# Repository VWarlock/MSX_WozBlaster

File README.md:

# MSX WozBlaster
MSX OPL4 FM &amp; Wavetable Sound Synthesizer

# WozBlaster version 1 Revision 2

All thruhole components was changed to SMT

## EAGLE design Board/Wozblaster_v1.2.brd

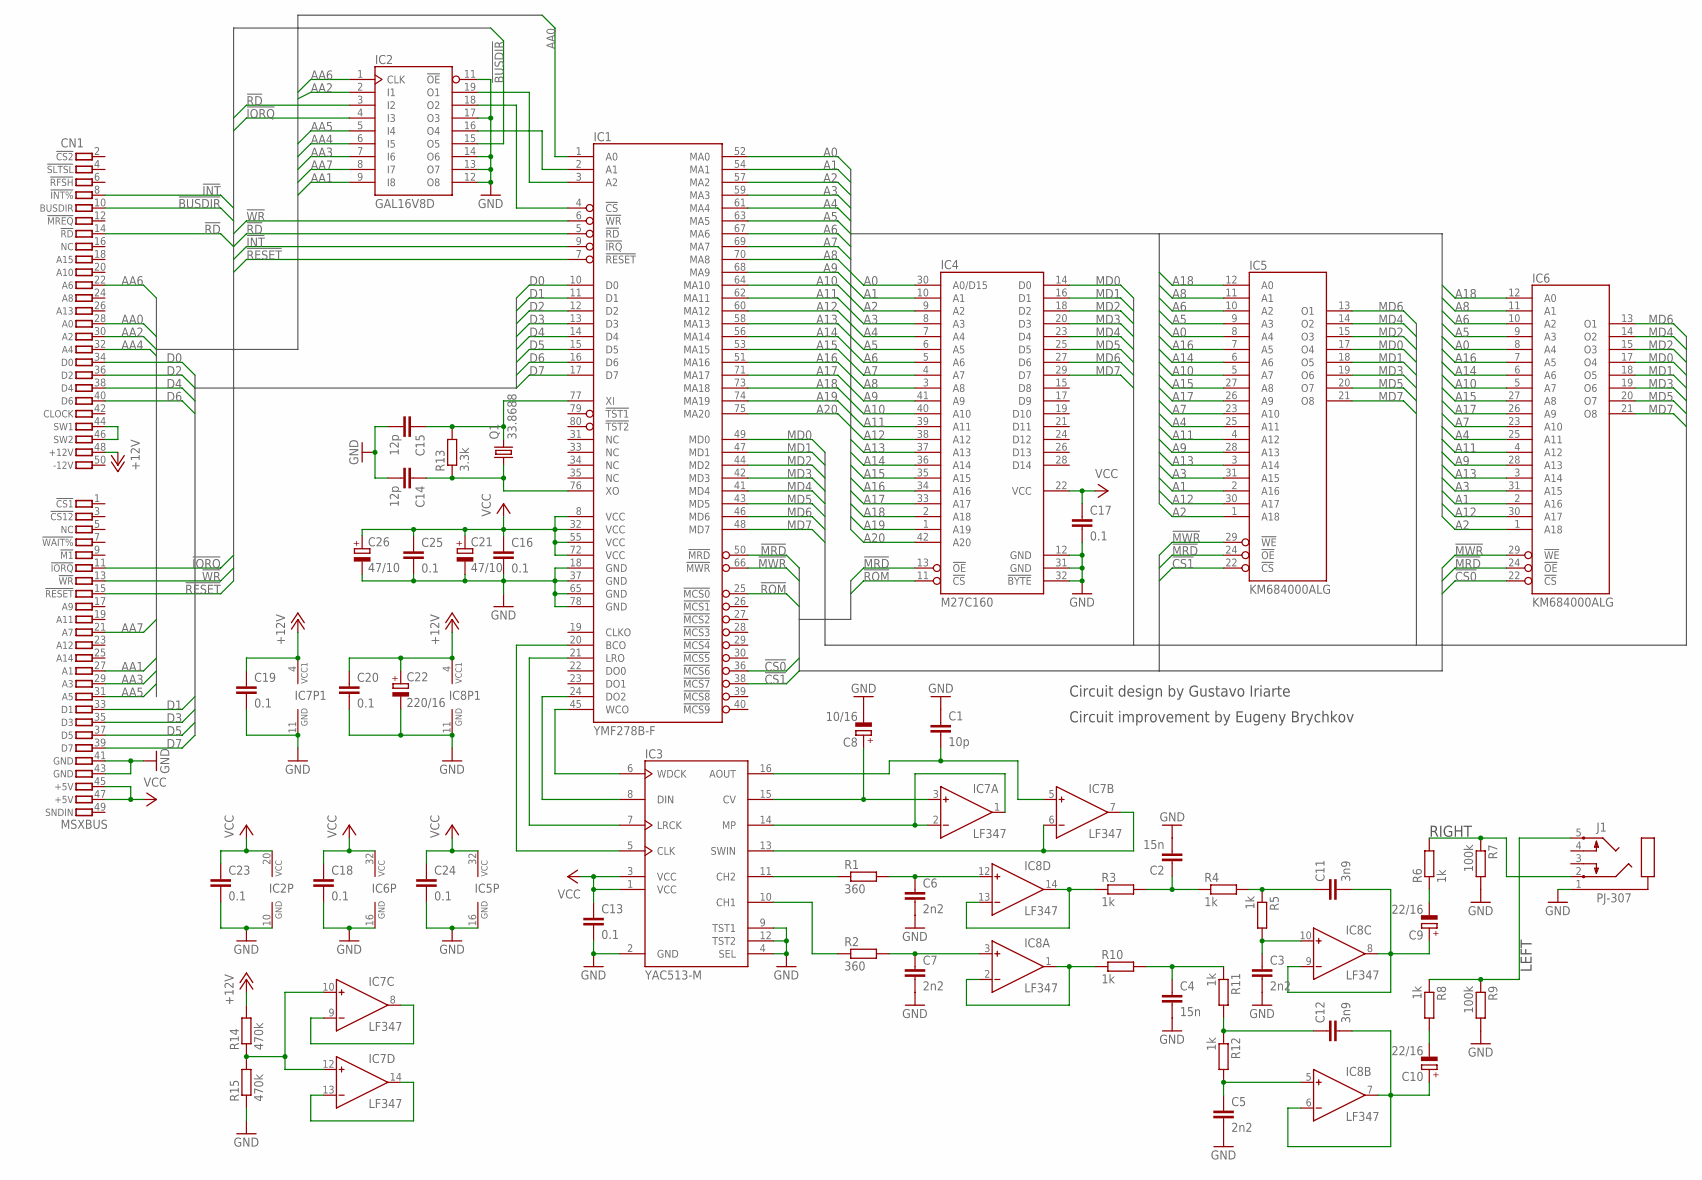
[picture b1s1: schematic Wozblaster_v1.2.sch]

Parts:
C1: 10p; C0805
C2, C4: 15n; C0805
C3, C5, C6, C7: 2n2; C0805
C8: 10/16; SMC_B
C9, C10: 22/16; SMC_B
C11, C12: 3n9; C0805
C13, C16, C17, C18, C19, C20, C23, C24, C25: 0.1; C0805
C14, C15: 12p; C0805
C21, C26: 47/10; SMC_B
C22: 220/16; SMC_E
CN1: MSXBUS; MSXBUS_EDGECONN
IC1: YMF278B-F; 80-QFP
IC2: GAL16V8D; DIL20
IC3: YAC513-M; 16SOP
IC4: M27C160; DIL42
IC5, IC6: KM684000ALG; SOP32L
IC7, IC8: LF347; SO14-2
J1: PJ-307
Q1: 33.8688; HC49/S
R1, R2: 360; R0805
R3, R4, R5, R6, R8, R10, R11, R12: 1k; R0805
R7, R9: 100k; R0805
R13: 3.3k; R0805
R14, R15: 470k; R0805

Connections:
!BUSDIR: CN1.10 (10.BUSDIR), IC2.15 (O5)
!CS0: IC1.36 (!MCS6), IC6.22 (!CS)
!CS1: IC1.38 (!MCS7), IC5.22 (!CS)
!INT: CN1.8 (8.!INT%), IC1.9 (!IRQ)
!IORQ: CN1.11 (11.!IORQ), IC2.4 (I3)
!MRD: IC1.50 (!MRD), IC4.13 (!OE), IC5.24 (!OE), IC6.24 (!OE)
!MWR: IC1.66 (!MWR), IC5.29 (!WE), IC6.29 (!WE)
!RD: CN1.14 (14.!RD), IC1.5 (!RD), IC2.3 (I2)
!RESET: CN1.15 (15.!RESET), IC1.7 (!RESET)
!ROM: IC1.25 (!MCS0), IC4.11 (!CS)
!WR: CN1.13 (13.!WR), IC1.6 (!WR)
+12V: C19.1, C20.1, C22.+, CN1.48 (48.+12V), IC7.4 (VCC), IC8.4 (VCC), R14.2
A0: IC1.52 (MA0), IC4.30 (A0/D15), IC5.8 (A4), IC6.8 (A4)
A1: IC1.54 (MA1), IC4.10 (A1), IC5.2 (A16), IC6.2 (A16)
A2: IC1.57 (MA2), IC4.9 (A2), IC5.1 (A18), IC6.1 (A18)
A3: IC1.59 (MA3), IC4.8 (A3), IC5.31 (A15), IC6.31 (A15)
A4: IC1.61 (MA4), IC4.7 (A4), IC5.25 (A11), IC6.25 (A11)
A5: IC1.63 (MA5), IC4.6 (A5), IC5.9 (A3), IC6.9 (A3)
A6: IC1.67 (MA6), IC4.5 (A6), IC5.10 (A2), IC6.10 (A2)
A7: IC1.69 (MA7), IC4.4 (A7), IC5.23 (A10), IC6.23 (A10)
A8: IC1.70 (MA8), IC4.3 (A8), IC5.11 (A1), IC6.11 (A1)
A9: IC1.68 (MA9), IC4.41 (A9), IC5.28 (A13), IC6.28 (A13)
A10: IC1.64 (MA10), IC4.40 (A10), IC5.5 (A7), IC6.5 (A7)
A11: IC1.62 (MA11), IC4.39 (A11), IC5.4 (A12), IC6.4 (A12)
A12: IC1.60 (MA12), IC4.38 (A12), IC5.30 (A17), IC6.30 (A17)
A13: IC1.58 (MA13), IC4.37 (A13), IC5.3 (A14), IC6.3 (A14)
A14: IC1.56 (MA14), IC4.36 (A14), IC5.6 (A6), IC6.6 (A6)
A15: IC1.53 (MA15), IC4.35 (A15), IC5.27 (A8), IC6.27 (A8)
A16: IC1.51 (MA16), IC4.34 (A16), IC5.7 (A5), IC6.7 (A5)
A17: IC1.71 (MA17), IC4.33 (A17), IC5.26 (A9), IC6.26 (A9)
A18: IC1.73 (MA18), IC4.2 (A18), IC5.12 (A0), IC6.12 (A0)
A19: IC1.74 (MA19), IC4.1 (A19)
A20: IC1.75 (MA20), IC4.42 (A20)
AA0: CN1.28 (28.A0), IC1.1 (A0)
AA1: CN1.27 (27.A1), IC2.9 (I8)
AA2: CN1.30 (30.A2), IC2.2 (I1)
AA3: CN1.29 (29.A3), IC2.7 (I6)
AA4: CN1.32 (32.A4), IC2.6 (I5)
AA5: CN1.31 (31.A5), IC2.5 (I4)
AA6: CN1.22 (22.A6), IC2.1 (CLK)
AA7: CN1.21 (21.A7), IC2.8 (I7)
D0: CN1.34 (34.D0), IC1.10 (D0)
D1: CN1.33 (33.D1), IC1.11 (D1)
D2: CN1.36 (36.D2), IC1.12 (D2)
D3: CN1.35 (35.D3), IC1.13 (D3)
D4: CN1.38 (38.D4), IC1.14 (D4)
D5: CN1.37 (37.D5), IC1.15 (D5)
D6: CN1.40 (40.D6), IC1.16 (D6)
D7: CN1.39 (39.D7), IC1.17 (D7)
GND: C1.1, C2.2, C3.2, C4.2, C5.2, C6.2, C7.2, C8.-, C13.2, C14.2, C15.2, C16.2, C17.2, C18.2, C19.2, C20.2, C21.-, C22.-, C23.2, C24.2, C25.2, C26.-, CN1.41 (41.GND), CN1.43 (43.GND), IC1.18 (GND), IC1.37 (GND), IC1.65 (GND), IC1.78 (GND), IC2.10 (GND), IC2.11 (!OE), IC2.12 (O8), IC2.13 (O7), IC2.14 (O6), IC2.17 (O3), IC3.2 (GND), IC3.4 (SEL), IC3.9 (TST1), IC3.12 (TST2), IC4.12 (GND), IC4.31 (GND), IC4.32 (!BYTE), IC5.16 (GND), IC6.16 (GND), IC7.11 (GND), IC8.11 (GND), J1.1, R7.2, R9.2, R15.1
MD0: IC1.49 (MD0), IC4.14 (D0), IC5.17 (O4), IC6.17 (O4)
MD1: IC1.47 (MD1), IC4.16 (D1), IC5.18 (O5), IC6.18 (O5)
MD2: IC1.44 (MD2), IC4.18 (D2), IC5.15 (O3), IC6.15 (O3)
MD3: IC1.42 (MD3), IC4.20 (D3), IC5.19 (O6), IC6.19 (O6)
MD4: IC1.41 (MD4), IC4.23 (D4), IC5.14 (O2), IC6.14 (O2)
MD5: IC1.43 (MD5), IC4.25 (D5), IC5.20 (O7), IC6.20 (O7)
MD6: IC1.46 (MD6), IC4.27 (D6), IC5.13 (O1), IC6.13 (O1)
MD7: IC1.48 (MD7), IC4.29 (D7), IC5.21 (O8), IC6.21 (O8)
unnamed: C5.1, IC8.5 (IN+), R12.2
unnamed: CN1.44 (44.SW1), CN1.46 (46.SW2)
unnamed: IC7.10 (IN+), IC7.12 (IN+), R14.1, R15.2
unnamed: IC7.8 (OUT), IC7.9 (IN-)
unnamed: IC7.13 (IN-), IC7.14 (OUT)
unnamed: IC1.3 (A2), IC2.19 (O1)
unnamed: IC1.4 (!CS), IC2.18 (O2)
unnamed: IC1.2 (A1), IC2.16 (O4)
unnamed: C1.2, IC3.16 (AOUT), IC7.5 (IN+)
unnamed: IC3.14 (MP), IC7.1 (OUT), IC7.2 (IN-)
unnamed: IC3.11 (CH2), R1.1
unnamed: C6.1, IC8.12 (IN+), R1.2
unnamed: IC8.13 (IN-), IC8.14 (OUT), R3.1
unnamed: C2.1, R3.2, R4.1
unnamed: C11.1, R4.2, R5.1
unnamed: C3.1, IC8.10 (IN+), R5.2
unnamed: C9.+, C11.2, IC8.8 (OUT), IC8.9 (IN-)
unnamed: C10.-, R8.2
unnamed: J1.2, R6.2, R7.1
unnamed: C7.1, IC8.3 (IN+), R2.2
unnamed: IC8.1 (OUT), IC8.2 (IN-), R10.1
unnamed: C4.1, R10.2, R11.1
unnamed: C12.1, R11.2, R12.1
unnamed: C10.+, C12.2, IC8.6 (IN-), IC8.7 (OUT)
unnamed: C9.-, R6.1
unnamed: J1.5, R8.1, R9.1
unnamed: IC3.10 (CH1), R2.1
unnamed: C8.+, IC3.15 (CV), IC7.3 (IN+)
unnamed: IC3.13 (SWIN), IC7.6 (IN-), IC7.7 (OUT)
unnamed: IC1.20 (BCO), IC3.5 (CLK)
unnamed: IC1.45 (WCO), IC3.6 (WDCK)
unnamed: IC1.21 (LRO), IC3.7 (LRCK)
unnamed: IC1.24 (DO2), IC3.8 (DIN)
unnamed: C15.1, IC1.77 (XI), Q1.2, R13.2
unnamed: C14.1, IC1.76 (XO), Q1.1, R13.1
VCC: C13.1, C16.1, C17.1, C18.1, C21.+, C23.1, C24.1, C25.1, C26.+, CN1.45 (45.+5V), CN1.47 (47.+5V), IC1.8 (VCC), IC1.32 (VCC), IC1.55 (VCC), IC1.72 (VCC), IC2.20 (VCC), IC3.1 (VCC), IC3.3 (VCC), IC4.22 (VCC), IC5.32 (VCC), IC6.32 (VCC)

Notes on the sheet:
Circuit design by Gustavo Iriarte
Circuit improvement by Eugeny Brychkov
LEFT
RIGHT

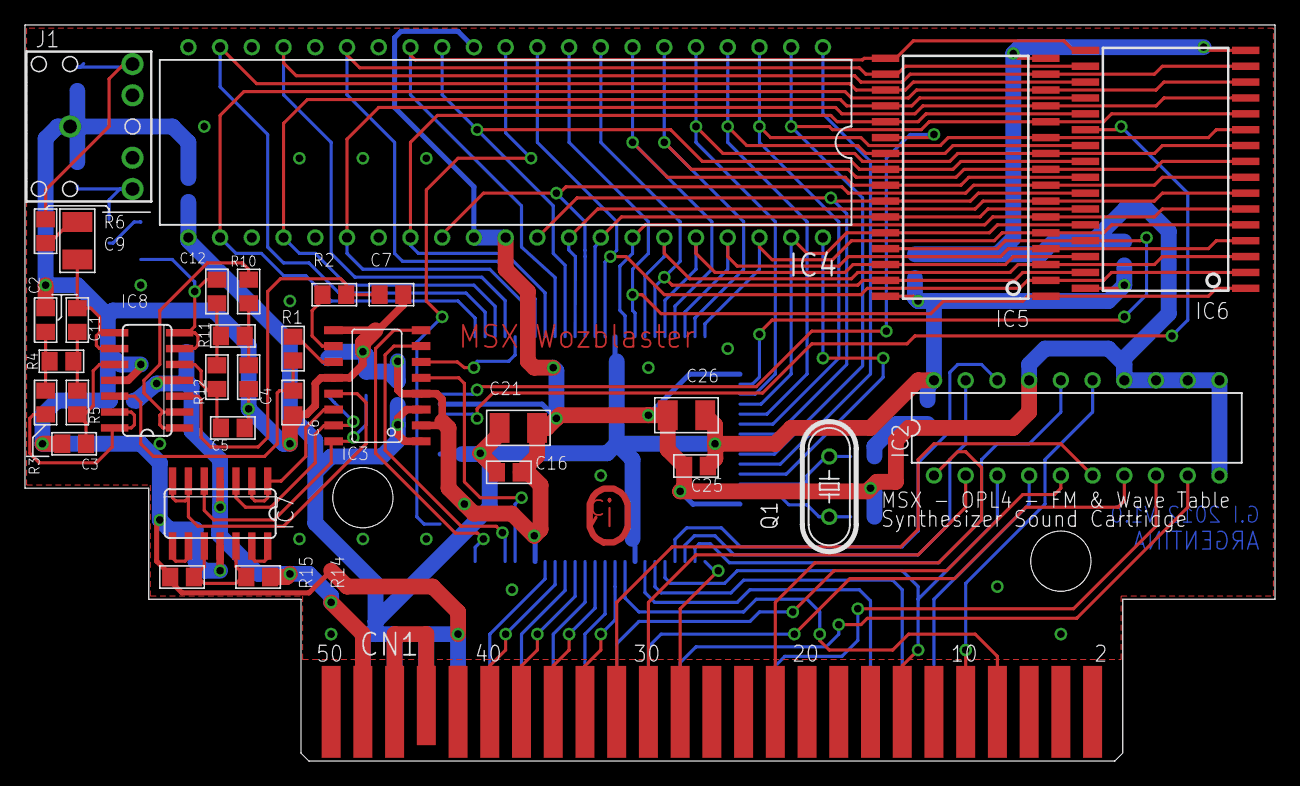
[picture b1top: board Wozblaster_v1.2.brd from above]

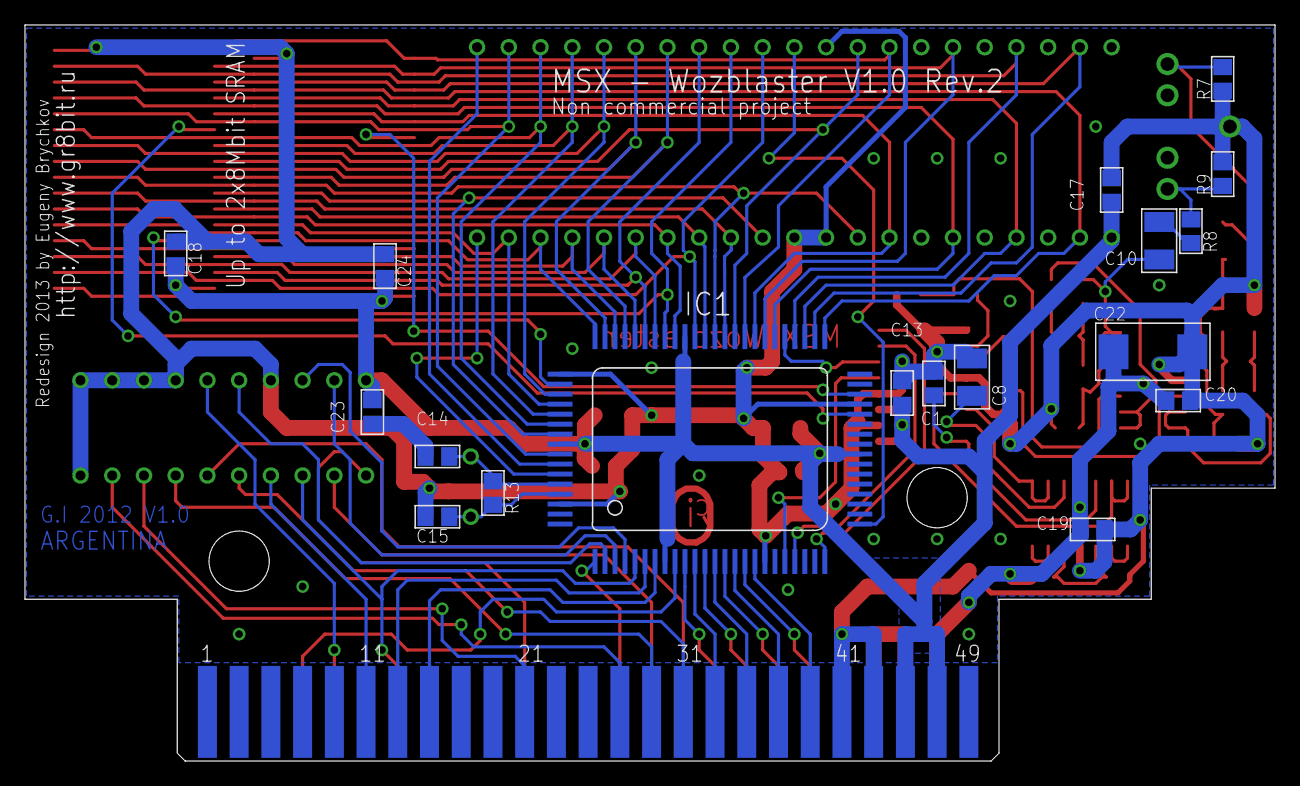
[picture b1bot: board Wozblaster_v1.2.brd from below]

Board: 2 copper layers, 100.1 x 58.9 mm, 52 parts (18 on the bottom side), 94 nets.

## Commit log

2023-05-25 Board Revision 1
2023-05-25 Board Revision 2
